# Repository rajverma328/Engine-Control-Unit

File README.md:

# Engine Control Unit (ECU) - Engine Research Laboratory (ERL), IIT Kanpur

<table>
  <tr>
    <td></td>
    <td></td>
  </tr>
</table>

Welcome to the Engine Control Unit (ECU) repository of the Engine Research Laboratory (ERL) at the Indian Institute of Technology Kanpur (IIT Kanpur). In this README, we will explore the significance of ECU, what it is, and how it plays a crucial role in modern engine research and development.

## Table of Contents
- [Introduction](#introduction)
- [Custom designed PCB](#custom-designed-pcb)
- [3D model](#3d-model)
- [Features](#features)
- [Getting Started](#getting-started)
- [License](#license)

---

## Introduction

The Engine Control Unit (ECU) is a vital component of modern internal combustion engines, serving as the "brain" that controls various aspects of engine operation. At the Engine Research Laboratory (ERL) at IIT Kanpur, we have developed an advanced ECU system to facilitate cutting-edge research and development in the field of internal combustion engines.

### Custom designed PCB

### [3D model](https://sketchfab.com/models/28feef1cc19342ffbb0c7c30adc009e6/embed?autostart=1)
Click the above heading to view a 3D model of the Engine Control Unit

### Precision Control
ECUs are crucial for optimizing the performance of internal combustion engines. They monitor and control critical parameters such as fuel injection timing, air-fuel mixture, ignition timing, and exhaust emissions. This precise control leads to improved fuel efficiency, reduced emissions, and enhanced engine performance.

### Adaptability
Modern ECUs are highly adaptable, allowing engine performance to be optimized under different operating conditions. They can adjust engine parameters in real-time to respond to changes in load, temperature, altitude, and other factors. This adaptability ensures that the engine operates efficiently and reliably in various environments.

### Emission Compliance
ECUs play a significant role in meeting stringent emission regulations. By precisely controlling combustion and exhaust processes, they help reduce harmful emissions such as nitrogen oxides (NOx), carbon monoxide (CO), and particulate matter (PM), contributing to a cleaner environment.

### Data Collection and Analysis
ECUs also serve as data hubs, collecting a vast amount of data from various engine sensors. Researchers at ERL can use this data to analyze engine performance, identify potential issues, and fine-tune engine designs.

## Features

Our ECU developed at ERL, IIT Kanpur, offers the following features:

- **Real-time Control**: The ECU provides real-time control of engine parameters for precise and efficient operation.
- **Adaptive Algorithms**: Adaptive algorithms ensure optimal engine performance across various operating conditions.
- **Data Logging**: Extensive data logging capabilities for research and analysis purposes.
- **Open Source**: Our ECU system is open-source, allowing researchers to modify and customize it for specific projects.
- **User-Friendly Interface**: An intuitive interface for configuring and monitoring engine parameters.

## Getting Started

To get started with our ECU system, follow these steps:

1. Clone this repository to your local machine.
2. Review the documentation in the `docs` folder for installation and usage instructions.
3. Connect the ECU to your test engine according to the provided guidelines.
4. Use the provided software tools to configure and monitor the ECU's operation.

For detailed installation and usage instructions, please refer to the documentation.

## License

This ECU system is open-source software released under the [MIT License](LICENSE). Feel free to use, modify, and distribute it in accordance with the license terms.

---

Thank you for your interest in the Engine Control Unit developed at the Engine Research Laboratory (ERL), IIT Kanpur. If you have any questions or would like to collaborate, please don't hesitate to [contact us](mailto:akag@iitk.ac.in)

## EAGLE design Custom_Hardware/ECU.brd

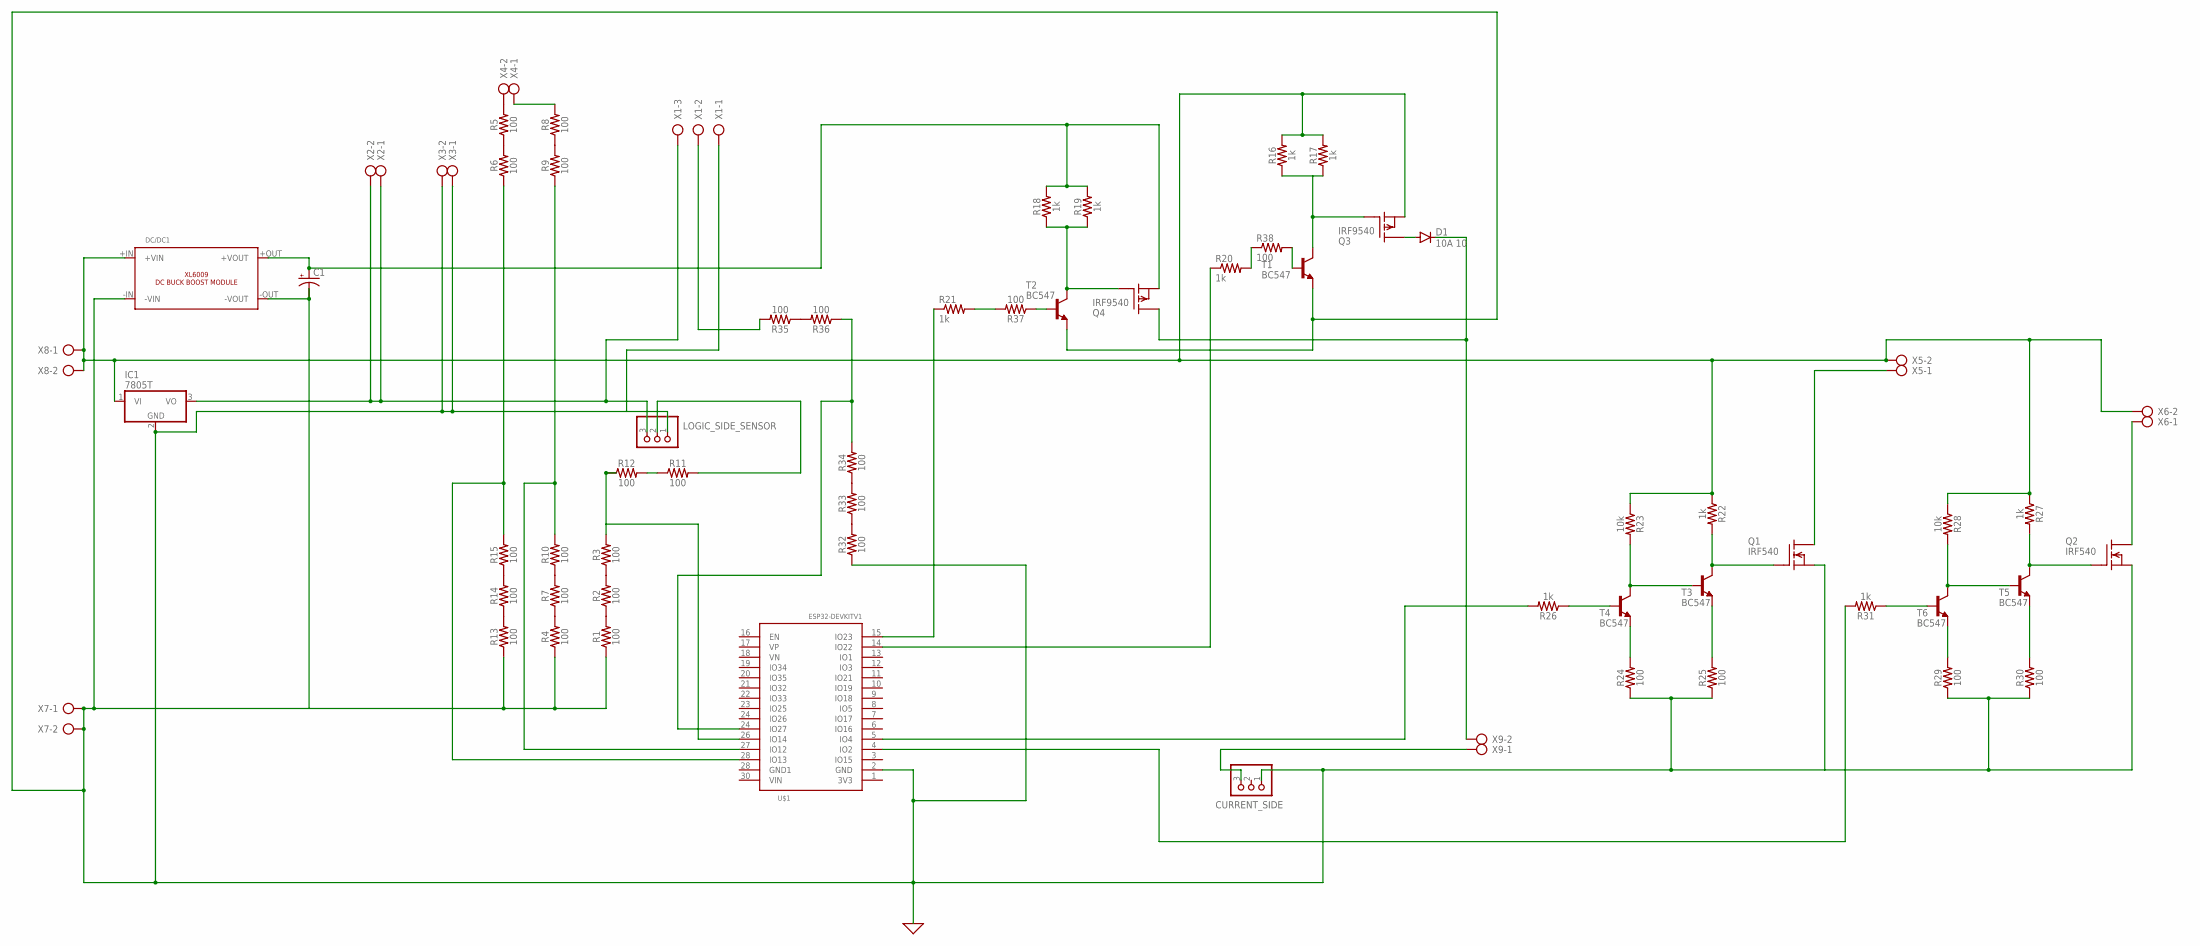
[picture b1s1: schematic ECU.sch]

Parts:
C1: CPOL-USE7.5-18; E7,5-18
CURRENT_SIDE: PINHD-1X3; 1X03
D1: 10A 10; DO201-15
DC/DC1: XL6009_DC_BUCK_BOOST_MODULE
IC1: 7805T; TO220H
LOGIC_SIDE_SENSOR: PINHD-1X3; 1X03
Q1, Q2: IRF540; TO220
Q3, Q4: IRF9540; TO220
R1, R2, R3, R4, R5, R6, R7, R8, R9, R10, R11, R12, R13, R14, R15, R24, R25, R29, R30, R32, R33, R34, R35, R36, R37: 100; AXIAL-0.3
R16, R17, R18, R19, R22, R26, R27, R31: 1k; AXIAL-0.3
R20, R21: 1k; 0207/12
R23, R28: 10k; AXIAL-0.3
R38: 100; 0207/12
T1, T2, T3, T4, T5, T6: BC547; TO92
U$1: ESP32DEVKITV1; ESP32-DEVKITV1
X1: AK300/3
X2, X3, X4, X5, X6, X7, X8, X9: AK300/2

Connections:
0: C1.-, CURRENT_SIDE.1, DC/DC1.-IN (-VIN), DC/DC1.-OUT (-VOUT), IC1.2 (GND), LOGIC_SIDE_SENSOR.1, Q1.3 (S), Q2.3 (S), R1.P$1 (1), R4.P$1 (1), R13.P$1 (1), R24.P$1 (1), R25.P$1 (1), R29.P$1 (1), R30.P$1 (1), R32.P$1 (1), T1.1 (E), T2.1 (E), U$1.2 (GND), X1.1, X3.1, X3.2, X7.1, X7.2
unnamed: Q2.2 (D), X6.1
unnamed: R38.2, T1.2 (B)
unnamed: Q1.2 (D), X5.1
unnamed: R23.P$2 (2), T3.2 (B), T4.3 (C)
unnamed: CURRENT_SIDE.3, X9.1
unnamed: R8.P$1 (1), R9.P$2 (2)
unnamed: IC1.3 (VO), LOGIC_SIDE_SENSOR.3, X1.3, X2.1, X2.2
unnamed: D1.C, Q4.2 (D), X9.2
unnamed: R6.P$1 (1), R15.P$2 (2), U$1.28 (IO13)
unnamed: R4.P$2 (2), R7.P$1 (1)
unnamed: R7.P$2 (2), R10.P$1 (1)
unnamed: R1.P$2 (2), R2.P$1 (1)
unnamed: R5.P$2 (2), X4.2
unnamed: R5.P$1 (1), R6.P$2 (2)
unnamed: R9.P$1 (1), R10.P$2 (2), U$1.27 (IO12)
unnamed: R8.P$2 (2), X4.1
unnamed: LOGIC_SIDE_SENSOR.2, R11.P$2 (2)
unnamed: R11.P$1 (1), R12.P$2 (2)
unnamed: R2.P$2 (2), R3.P$1 (1)
unnamed: R3.P$2 (2), R12.P$1 (1), U$1.26 (IO14)
unnamed: R28.P$2 (2), T5.2 (B), T6.3 (C)
unnamed: R13.P$2 (2), R14.P$1 (1)
unnamed: R14.P$2 (2), R15.P$1 (1)
unnamed: D1.A, Q3.2 (D)
unnamed: R24.P$2 (2), T4.1 (E)
unnamed: Q3.1 (G), R16.P$1 (1), R17.P$1 (1), T1.3 (C)
unnamed: C1.+, DC/DC1.+OUT (+VOUT), Q4.3 (S), R18.P$2 (2), R19.P$2 (2)
unnamed: Q4.1 (G), R18.P$1 (1), R19.P$1 (1), T2.3 (C)
unnamed: Q1.1 (G), R22.P$2 (2), T3.3 (C)
unnamed: R21.2, R37.P$2 (2)
unnamed: R21.1, U$1.15 (IO23)
unnamed: R25.P$2 (2), T3.1 (E)
unnamed: R20.1, U$1.14 (IO22)
unnamed: R26.P$1 (1), T4.2 (B)
unnamed: Q2.1 (G), R27.P$2 (2), T5.3 (C)
unnamed: DC/DC1.+IN (+VIN), IC1.1 (VI), Q3.3 (S), R16.P$2 (2), R17.P$2 (2), R22.P$1 (1), R23.P$1 (1), R27.P$1 (1), R28.P$1 (1), X5.2, X6.2, X8.1, X8.2
unnamed: R29.P$2 (2), T6.1 (E)
unnamed: R30.P$2 (2), T5.1 (E)
unnamed: R37.P$1 (1), T2.2 (B)
unnamed: R31.P$1 (1), T6.2 (B)
unnamed: R31.P$2 (2), U$1.4 (IO2)
unnamed: R26.P$2 (2), U$1.5 (IO4)
unnamed: R20.2, R38.1
unnamed: R32.P$2 (2), R33.P$1 (1)
unnamed: R33.P$2 (2), R34.P$1 (1)
unnamed: R35.P$1 (1), R36.P$2 (2)
unnamed: R34.P$2 (2), R36.P$1 (1), U$1.24 (IO27)
unnamed: R35.P$2 (2), X1.2

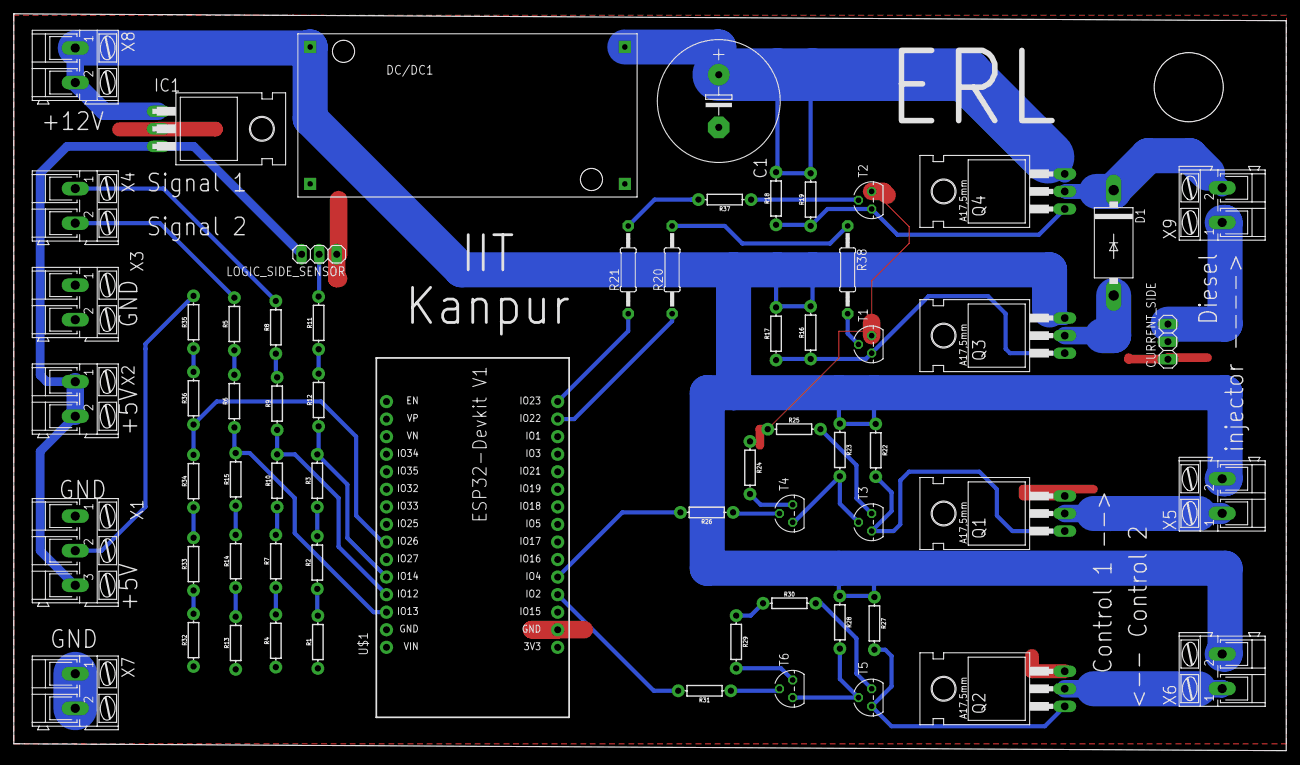
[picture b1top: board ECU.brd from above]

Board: 2 copper layers, 184.1 x 106.6 mm, 64 parts (0 on the bottom side), 49 nets.

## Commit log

2023-10-10 Commit 012:29 AM 10 October 2023
2023-10-10 October 10 12:12PM
2023-10-11 October 11 7;54 PM
2023-10-11 Commit 9:55 PM 12 October 2023
2023-10-12 October 12 test commit
2023-10-12 Commit 1:55 PM 12 October 2023
2023-10-15 October 15 2023 11:44 AM
2023-10-15 October 15 2023 13:03

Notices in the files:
parts and their libraries:
SparkFun-Resistors: Licensing: Creative Commons ShareAlike 4.0 International - https://creativecommons.org/licenses/by-sa/4.0
